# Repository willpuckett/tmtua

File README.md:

# TMTua

A drop-in fan connector for your Quiet Storm.

TMTua is smallish board with a single purpose: to connect a 4 pin (Noctua) fan
to your printer pcb without having to crimp a custom cable ever again.

## Features

- 3/4 pin fan connector
- No soldering required
- Voltage selection jumper (5V or Motor Voltage)

## Usage

1. Install the TMTua in a spare stepper driver slot on your printer pcb. Make
   sure the orientation is correct by aligning the top silk screen that says
   "EN" with the stepper driver slot's enable pin. If you install this
   backwards, bad things™ will happen.
2. Connect the fan to the TMTua using the 4 pin connector.
3. Set the voltage jumper to the desired voltage (5V or Motor Voltage). There is
   no buck on board, so if you have a 24V printer, you CANNOT use a 12V fan.
4. Match your stepper slot's pin numbers to the TMTua's pin numbers using the
   following table and your PCB's schematic/pinout diagram in your printer
   firmware.

| TMTua Pin | Stepper Driver Pin |
| --------- | ------------------ |
| fan0      |                    |
| tach0     | EN                 |
| tach1     | UART[^1]           |
| fan1      |                    |
| pwm0      | STEP               |
| pwm1      | DIR                |

## Example Klipper Configuration

```
[fan_generic fan_1]
pin: PA1
tachometer_pin: ^PD8
```

## Tachometer Pull-ups

You can use the
[Noctua white paper](https://noctua.at/pub/media/wysiwyg/Noctua_PWM_specifications_white_paper.pdf)
to assess whether the onboard pull-up if there's already one on the EN pin is
sufficient for the tach pins and your fans.

The paper outlines the following **minimum** recommendations:

| Voltage | Pullup Resistor(Ω) |
| ------- | ------------------ |
| 5V      | 1k                 |
| 12V     | 2k7                |
| 24V     | 12k                |

For example, the internal pull-ups on STM32F407 are about 40k which are
sufficient for all cases, but the hardware 10k pull-up on EN on my Robin Nano v3
board is too strong for a 24v fan, though fine for 5 and 12v fans.

## Schematic

## Where Do I Get One?

You can order the board from [JLCPCB](https://jlcpcb.com) using the
[production_files](jlcpcb/production_files) directory.

They're also available on my [here](https://octule.com).

[^1]: May not be wired on older boards. On newer boards, you may need to jumper
the UART pin under the stepper driver slot to connect it to your mcu. Consult
your board's schematic for more information.

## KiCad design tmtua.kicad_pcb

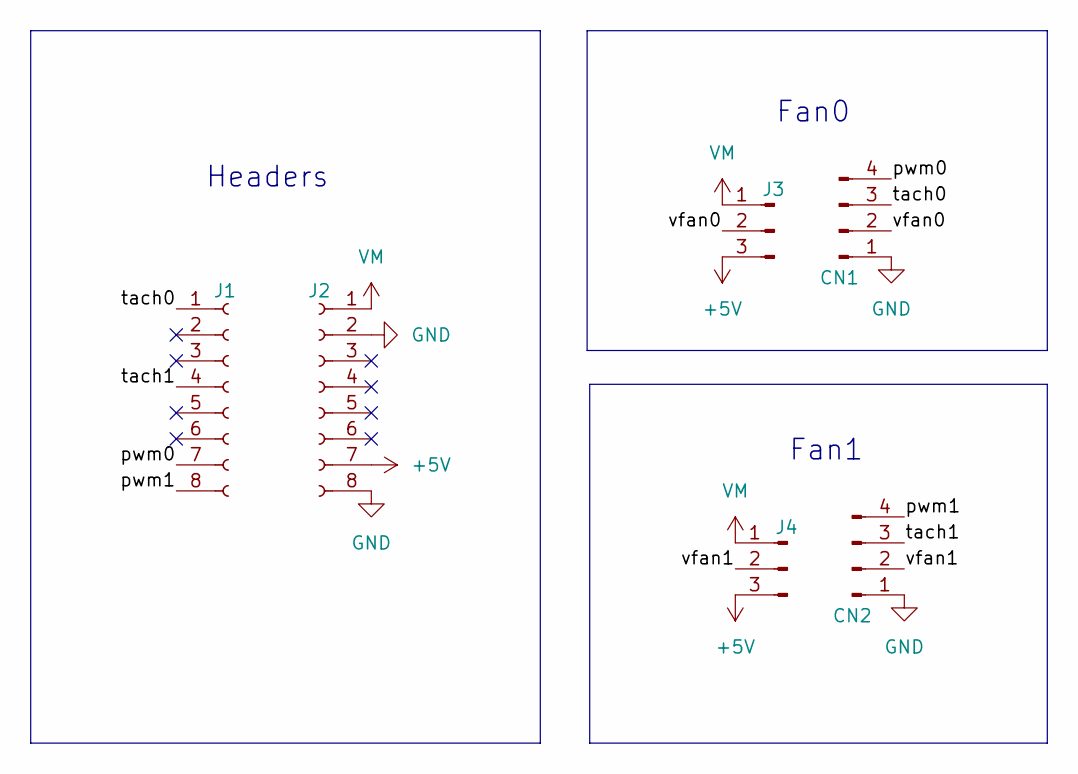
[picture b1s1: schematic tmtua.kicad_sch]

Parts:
CN1, CN2: HF1004E; FanPinHeader_1x04_P2.54mm_Vertical
J1, J2: B-2100S08P-A110; PinHeader_1x08_P2.54mm_Vertical
J3, J4: PZ200V-11-03P; PinHeader_1x03_P2.00mm_Vertical

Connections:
+5V: J2.7, J3.3, J4.3
/pwm0: CN1.4, J1.7
/pwm1: CN2.4, J1.8
/tach0: CN1.3, J1.1
/tach1: CN2.3, J1.4
/vfan0: CN1.2, J3.2
/vfan1: CN2.2, J4.2
GND: CN1.1, CN2.1, J2.2, J2.8
VM: J2.1, J3.1, J4.1

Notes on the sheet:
Fan1
Fan0
Headers

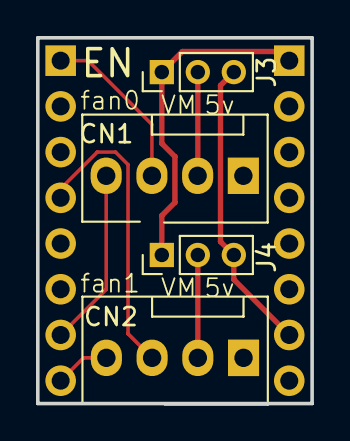
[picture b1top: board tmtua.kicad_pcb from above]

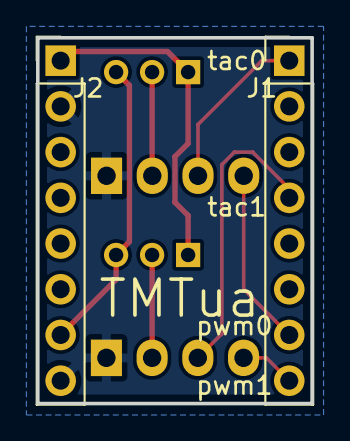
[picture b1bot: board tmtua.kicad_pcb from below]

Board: 2 copper layers, 15.2 x 20.3 mm, 6 parts (2 on the bottom side), 9 nets.

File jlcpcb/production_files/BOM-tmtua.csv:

Comment,Designator,Footprint,LCSC
B-2100S08P-A110,"J1,J2",PinHeader_1x08_P2.54mm_Vertical,C124381
HF1004E,"CN1,CN2",FanPinHeader_1x04_P2.54mm_Vertical,C2761402
PZ200V-11-03P,"J3,J4",PinHeader_1x03_P2.00mm_Vertical,C541857

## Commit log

2024-08-23 correct schematic
